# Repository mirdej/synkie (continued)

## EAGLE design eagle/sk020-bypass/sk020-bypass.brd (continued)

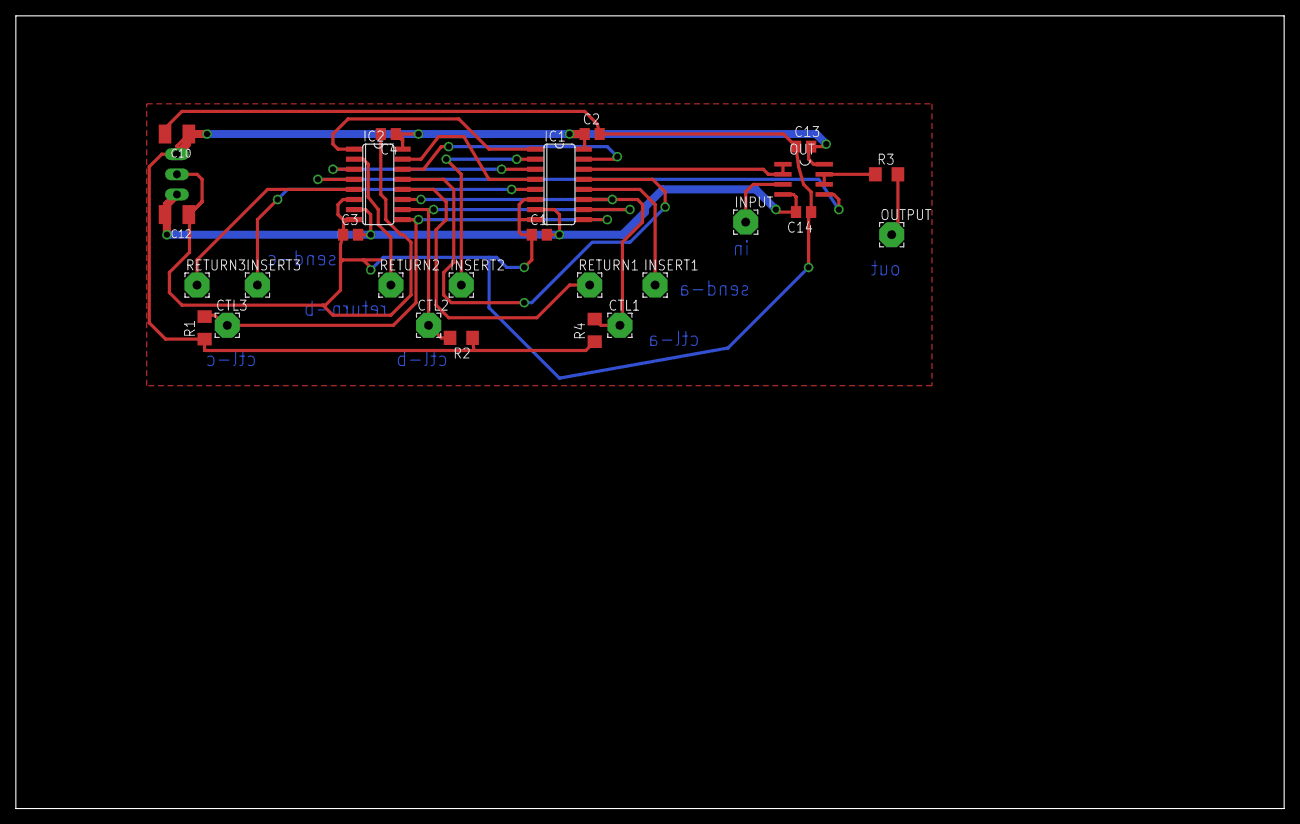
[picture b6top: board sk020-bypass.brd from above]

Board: 2 copper layers, 160.0 x 100.0 mm, 27 parts (1 on the bottom side), 22 nets.

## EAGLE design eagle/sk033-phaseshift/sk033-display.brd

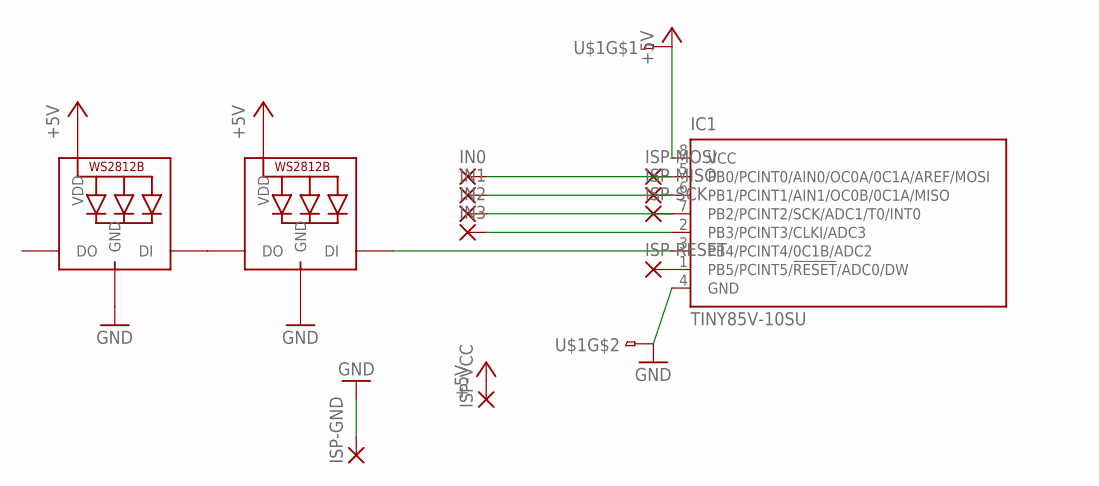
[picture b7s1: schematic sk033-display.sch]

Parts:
IC1: TINY85V-10SU; 8S2
IN0, IN1, IN2, IN3: SMD2
ISP-GND: SMD2
ISP-MISO: SMD2
ISP-MOSI: SMD2
ISP-RESET: SMD2
ISP-SCK: SMD2
ISP-VCC: SMD2
U$1: 2PIN-SMD-2.54
U$2, U$4: SK6812MINI

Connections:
+5V: IC1.8 (VCC), ISP-VCC.1, U$1.2, U$2.4 (VDD), U$4.4 (VDD)
GND: IC1.4 (GND), ISP-GND.1, U$1.3, U$2.2 (GND), U$4.2 (GND)
unnamed: IC1.1 (PB5/PCINT5/!RESET!/ADC0/DW), ISP-RESET.1
unnamed: U$2.1 (DO), U$4.3 (DI)
unnamed: IC1.3 (PB4/PCINT4/0C1B/ADC2), U$2.3 (DI)
unnamed: IC1.2 (PB3/PCINT3/CLKI/ADC3), IN3.1
unnamed: IC1.5 (PB0/PCINT0/AIN0/OC0A/0C1A/AREF/MOSI), IN0.1, ISP-MOSI.1
unnamed: IC1.6 (PB1/PCINT1/AIN1/OC0B/0C1A/MISO), IN1.1, ISP-MISO.1
unnamed: IC1.7 (PB2/PCINT2/SCK/ADC1/T0/INT0), IN2.1, ISP-SCK.1

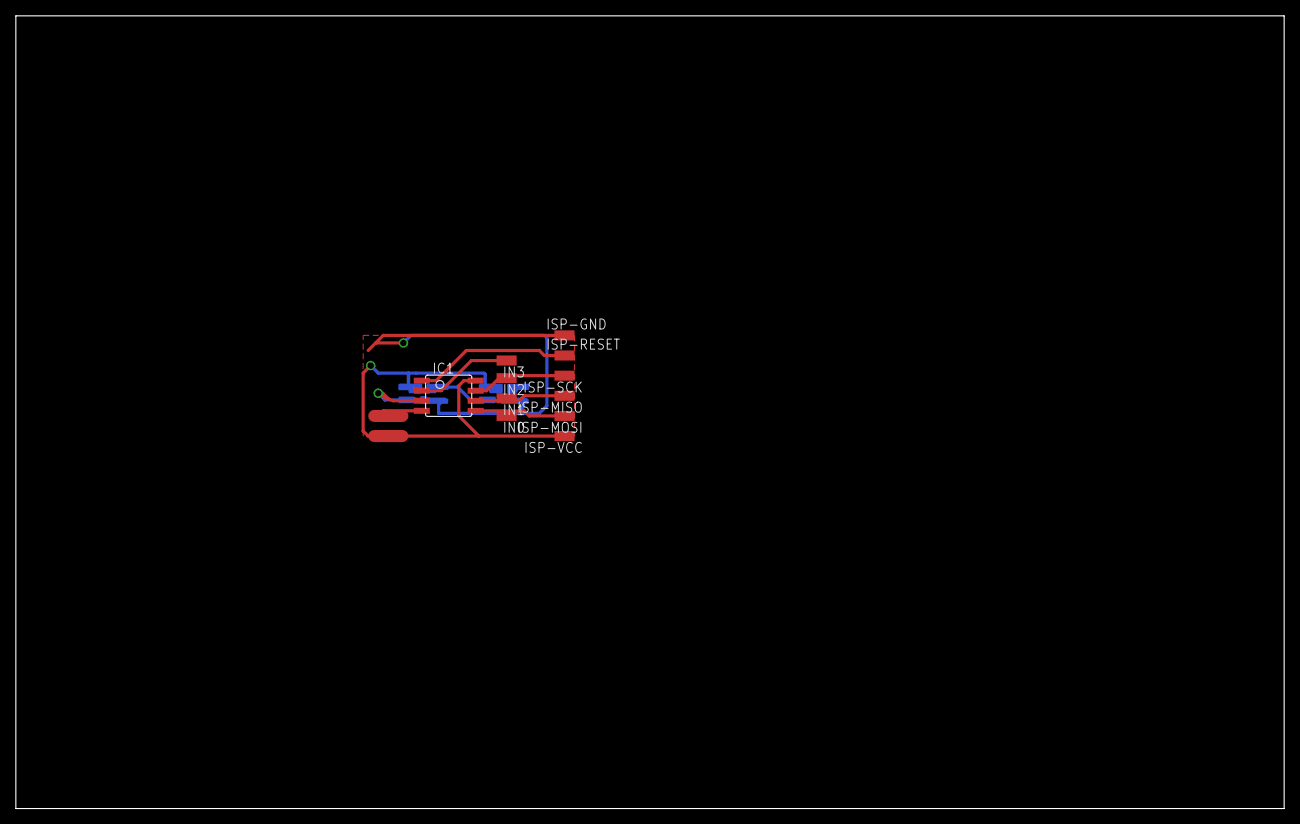
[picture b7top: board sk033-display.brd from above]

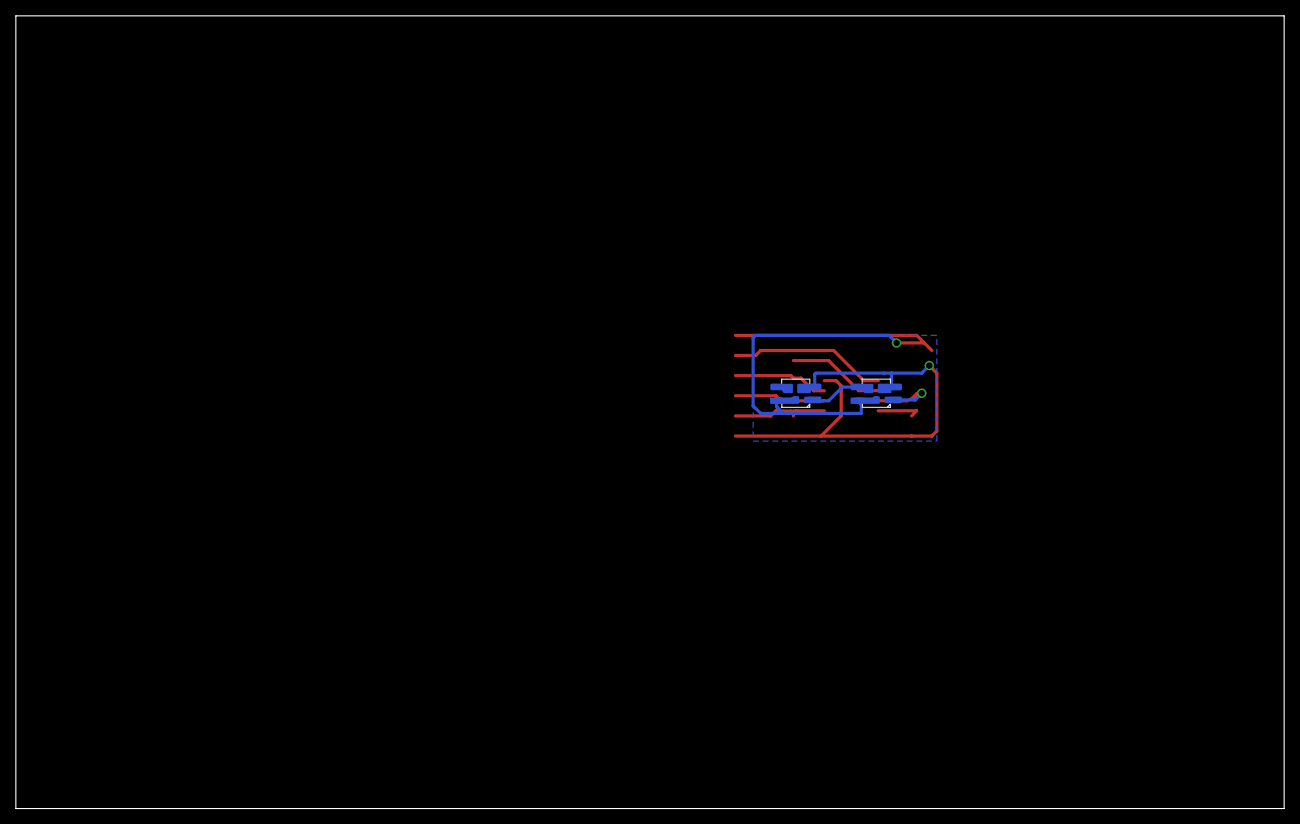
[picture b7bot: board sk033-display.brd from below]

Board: 2 copper layers, 160.0 x 100.0 mm, 14 parts (2 on the bottom side), 9 nets.

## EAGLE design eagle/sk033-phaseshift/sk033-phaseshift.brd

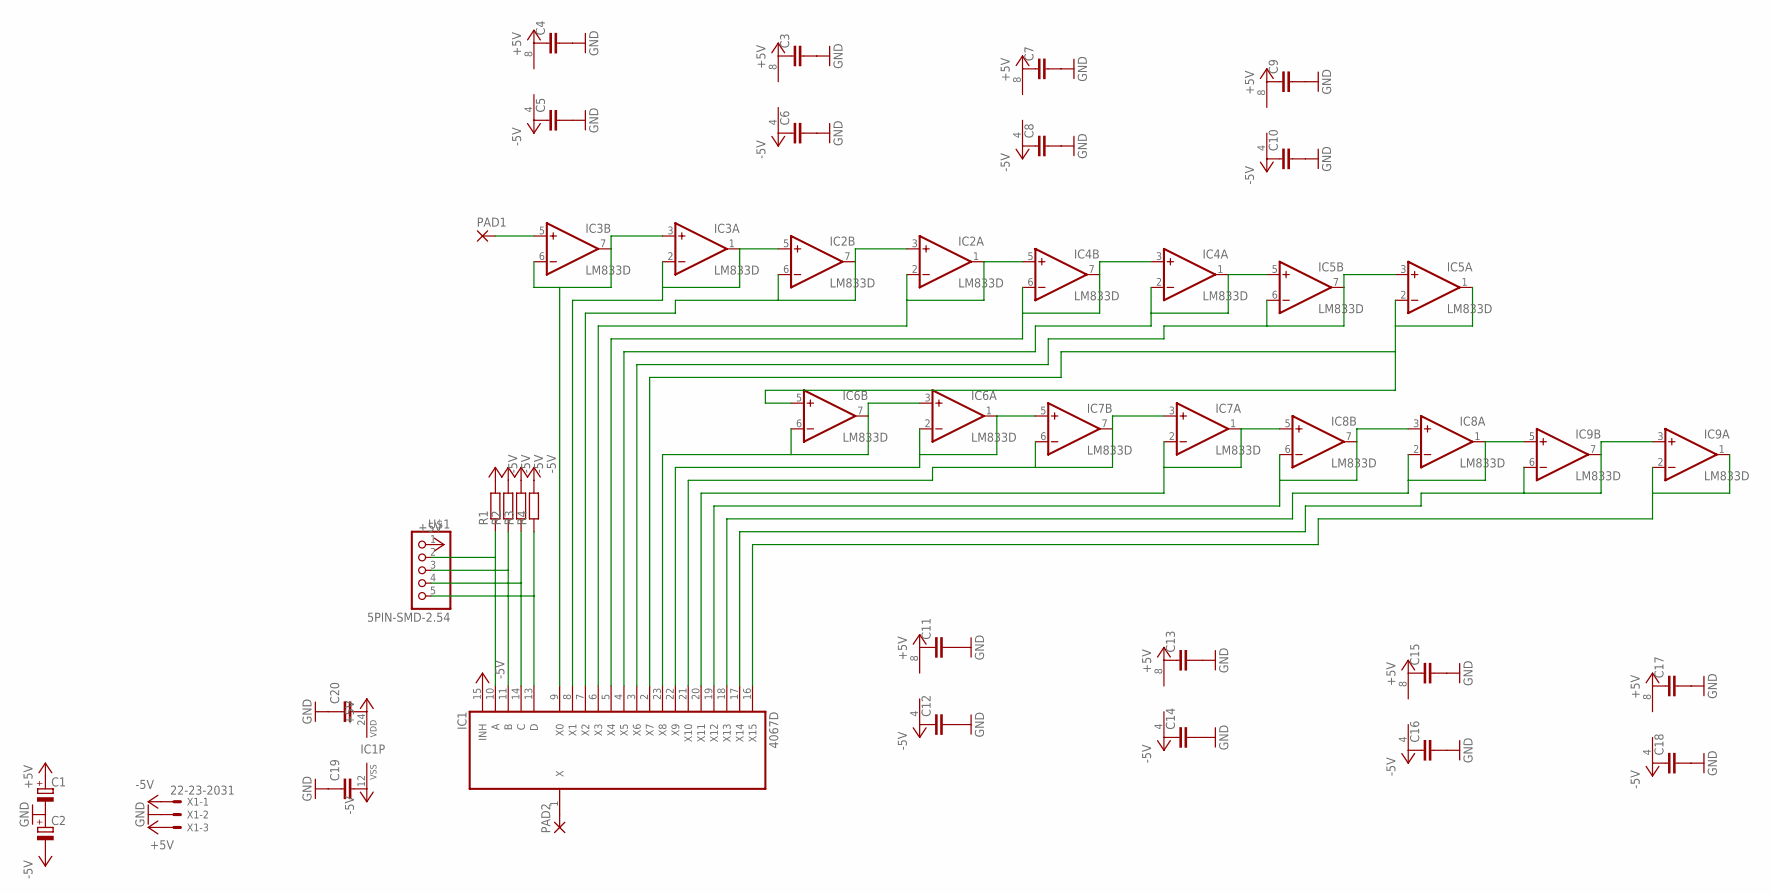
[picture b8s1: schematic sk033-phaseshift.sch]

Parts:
C1, C2: CPOL-EUSMCB; SMC_B
C3, C4, C5, C6, C7, C8, C9, C11, C12, C13, C14, C15, C16, C17, C18, C19: C-EUC1206; C1206
C10, C20: C-EUC0603; C0603
IC1: 4067D; SO24W
IC2, IC3, IC4, IC5, IC6, IC7, IC8, IC9: LM833D; SO08
PAD1, PAD2: 3,17/1,1
R1, R2, R3, R4: R-EU_R1206; R1206
U$1: 5PIN-SMD-2.54
X1: 22-23-2031

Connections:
+5V: C1.+, C3.1, C4.1, C7.1, C9.1, C11.1, C13.1, C15.1, C17.1, C20.2, IC1.24 (VDD), IC2.8 (V+), IC3.8 (V+), IC4.8 (V+), IC5.8 (V+), IC6.8 (V+), IC7.8 (V+), IC8.8 (V+), IC9.8 (V+), U$1.1, X1.3
-5V: C2.-, C5.1, C6.1, C8.1, C10.1, C12.1, C14.1, C16.1, C18.1, C19.2, IC1.12 (VSS), IC1.15 (INH), IC2.4 (V-), IC3.4 (V-), IC4.4 (V-), IC5.4 (V-), IC6.4 (V-), IC7.4 (V-), IC8.4 (V-), IC9.4 (V-), R1.2, R2.2, R3.2, R4.2, X1.1
GND: C1.-, C2.+, C3.2, C4.2, C5.2, C6.2, C7.2, C8.2, C9.2, C10.2, C11.2, C12.2, C13.2, C14.2, C15.2, C16.2, C17.2, C18.2, C19.1, C20.1, X1.2
unnamed: IC1.2 (X7), IC5.1 (OUT), IC5.2 (-IN), IC6.5 (+IN)
unnamed: IC1.7 (X2), IC2.3 (+IN), IC2.6 (-IN), IC2.7 (OUT)
unnamed: IC1.6 (X3), IC2.1 (OUT), IC2.2 (-IN), IC4.5 (+IN)
unnamed: IC1.5 (X4), IC4.3 (+IN), IC4.6 (-IN), IC4.7 (OUT)
unnamed: IC1.4 (X5), IC4.1 (OUT), IC4.2 (-IN), IC5.5 (+IN)
unnamed: IC1.3 (X6), IC5.3 (+IN), IC5.6 (-IN), IC5.7 (OUT)
unnamed: IC1.13 (D), R4.1, U$1.5
unnamed: IC1.23 (X8), IC6.3 (+IN), IC6.6 (-IN), IC6.7 (OUT)
unnamed: IC1.22 (X9), IC6.1 (OUT), IC6.2 (-IN), IC7.5 (+IN)
unnamed: IC1.21 (X10), IC7.3 (+IN), IC7.6 (-IN), IC7.7 (OUT)
unnamed: IC1.20 (X11), IC7.1 (OUT), IC7.2 (-IN), IC8.5 (+IN)
unnamed: IC1.19 (X12), IC8.3 (+IN), IC8.6 (-IN), IC8.7 (OUT)
unnamed: IC1.18 (X13), IC8.1 (OUT), IC8.2 (-IN), IC9.5 (+IN)
unnamed: IC1.17 (X14), IC9.3 (+IN), IC9.6 (-IN), IC9.7 (OUT)
unnamed: IC1.16 (X15), IC9.1 (OUT), IC9.2 (-IN)
unnamed: IC3.5 (+IN), PAD1.1
unnamed: IC1.9 (X0), IC3.3 (+IN), IC3.6 (-IN), IC3.7 (OUT)
unnamed: IC1.8 (X1), IC2.5 (+IN), IC3.1 (OUT), IC3.2 (-IN)
unnamed: IC1.14 (C), R3.1, U$1.4
unnamed: IC1.1 (X), PAD2.1
unnamed: IC1.11 (B), R2.1, U$1.3
unnamed: IC1.10 (A), R1.1, U$1.2

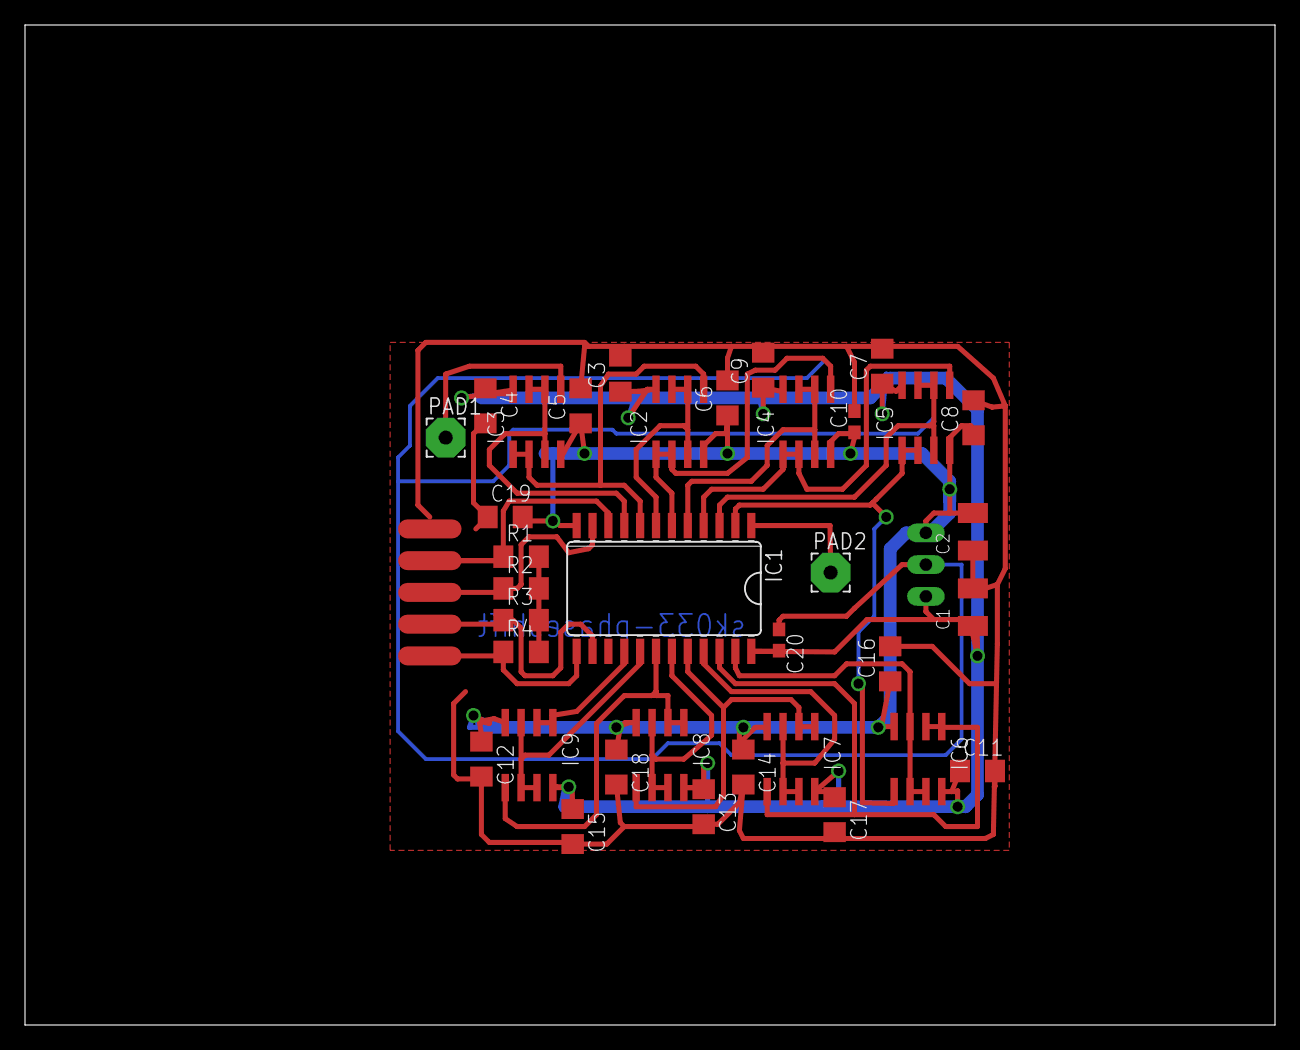
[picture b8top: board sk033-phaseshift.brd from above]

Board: 2 copper layers, 100.0 x 80.0 mm, 37 parts (1 on the bottom side), 25 nets.
